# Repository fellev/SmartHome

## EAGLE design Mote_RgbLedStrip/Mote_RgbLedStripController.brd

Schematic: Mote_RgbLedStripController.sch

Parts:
ANALOGSIDE: M13; 1X13
DIGITALSIDE: M13; 1X13
J1: CON_TERMINAL_BLOCK_02-5MM; TERMINAL_BLOCK_2P_5

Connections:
A0: ANALOGSIDE.1
A1: ANALOGSIDE.2
A2: ANALOGSIDE.3
A3: ANALOGSIDE.4
A4_SDA: ANALOGSIDE.5
A5_SCL: ANALOGSIDE.6
A6: ANALOGSIDE.7
A7: ANALOGSIDE.8
D0_RX: ANALOGSIDE.9
D1_TX: ANALOGSIDE.10
D2: DIGITALSIDE.12
D3: DIGITALSIDE.11
D4: DIGITALSIDE.10
D5: DIGITALSIDE.9
D6: DIGITALSIDE.8
D7: DIGITALSIDE.7
D8: DIGITALSIDE.6
D9: DIGITALSIDE.5
D10_SS: DIGITALSIDE.4
D11_MOSI: DIGITALSIDE.3
D12_MISO: DIGITALSIDE.2
D13_SCK: DIGITALSIDE.1
GND: ANALOGSIDE.13, J1.1
PWR: ANALOGSIDE.12, J1.2
RST: DIGITALSIDE.13
VCC: ANALOGSIDE.11

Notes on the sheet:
12V

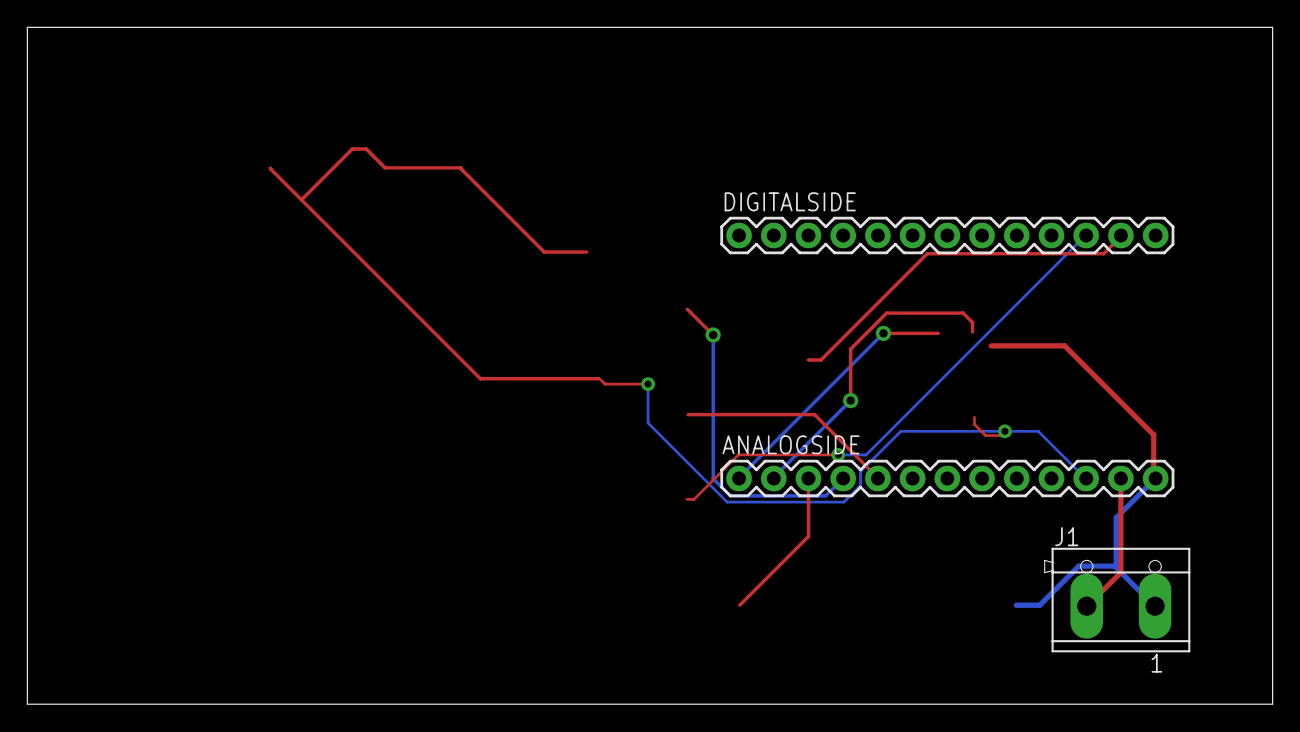
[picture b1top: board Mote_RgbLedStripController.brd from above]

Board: 2 copper layers, 91.1 x 49.5 mm, 3 parts (0 on the bottom side), 2 nets.

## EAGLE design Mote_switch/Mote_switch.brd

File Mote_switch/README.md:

Sync Mode
----------

Using SYNC mode (synchronize buttons on two SwitchMotes):

* Conect the sync wire to ground on switch you want to be controlled (the slave)
* Select the button mode (ON or OFF) by pressing the controlled button. Press the controlled button for 3 seonds. Now the switch in SYNC mode. Mode is ON when LED Duty Cycle is above 80% and OFF below 20%
* walk to the Mote_switch from which you want to control and ground the sync button and then press 3 seconds the button you want to be the controller (the master). At this point the master will broadcast a SYNC? token and the slave will respond with a SYNCx:y token where x=button placed in SYNC, y=mode of button placed in SYNC

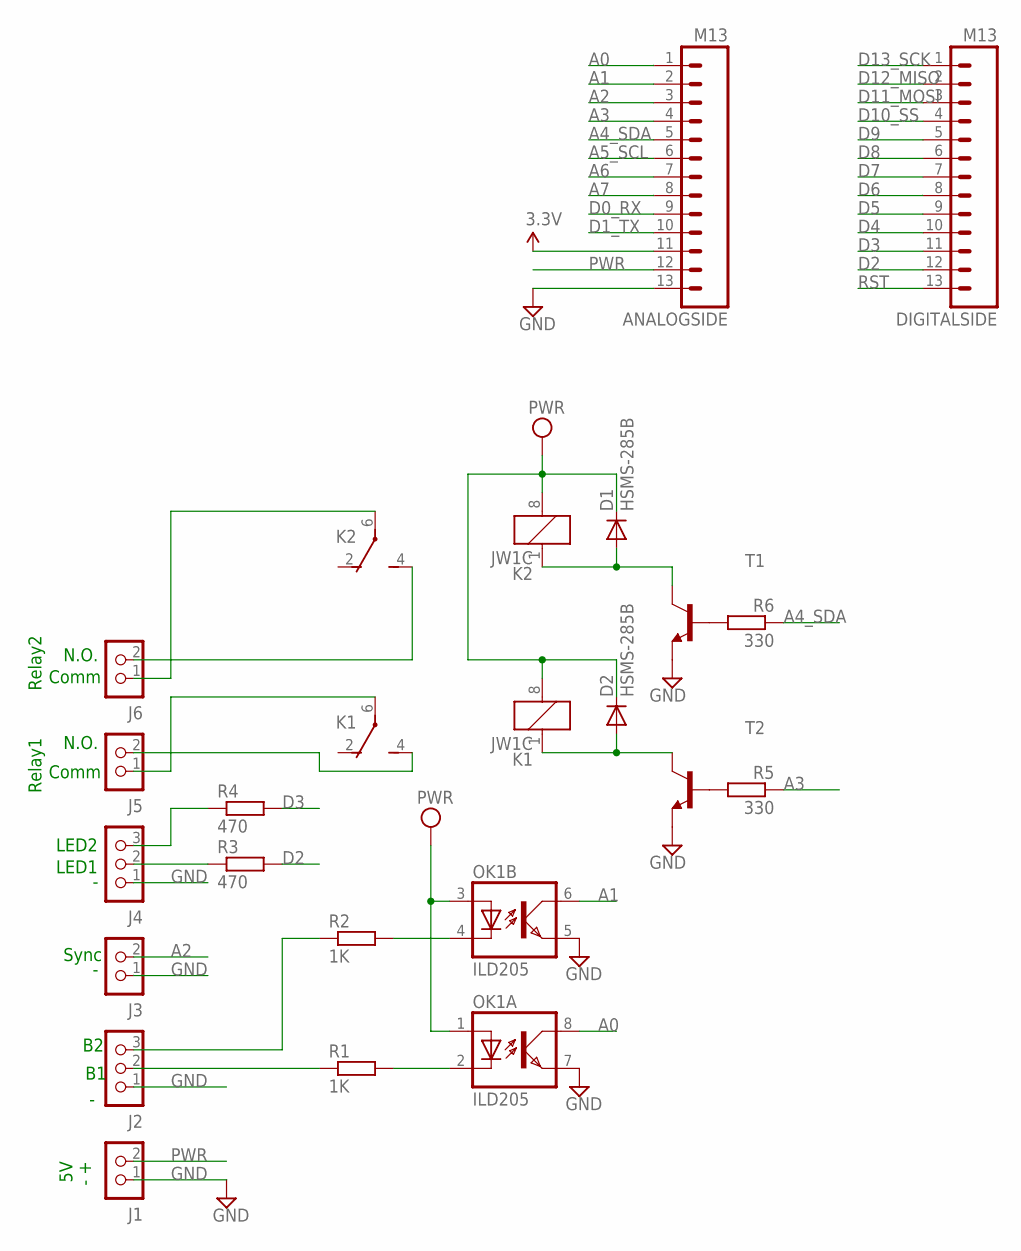
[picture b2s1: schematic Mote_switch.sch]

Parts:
ANALOGSIDE: M13; 1X13
D1, D2: HSMS-285B; SOT323
DIGITALSIDE: M13; 1X13
J1, J3, J5, J6: CON_TERMINAL_BLOCK_02-5MM; TERMINAL_BLOCK_2P_5
J2, J4: CON_TERMINAL_BLOCK_03-5MM; TERMINAL_BLOCK_3P_5
K1, K2: JW1C
OK1: ILD205; SOIC08
R1, R2: 1K; M2012
R3, R4: 470; M2012
R5, R6: 330; M2012
T1, T2: MMBT2222ALT1-NPN-SOT23-BEC; SOT23-BEC

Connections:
A0: ANALOGSIDE.1, OK1.8 (COL)
A1: ANALOGSIDE.2, OK1.6 (COL)
A2: ANALOGSIDE.3, J3.2
A3: ANALOGSIDE.4, R5.1
A4_SDA: ANALOGSIDE.5, R6.1
A5_SCL: ANALOGSIDE.6
A6: ANALOGSIDE.7
A7: ANALOGSIDE.8
D0_RX: ANALOGSIDE.9
D1_TX: ANALOGSIDE.10
D2: DIGITALSIDE.12, R3.2
D3: DIGITALSIDE.11, R4.2
D4: DIGITALSIDE.10
D5: DIGITALSIDE.9
D6: DIGITALSIDE.8
D7: DIGITALSIDE.7
D8: DIGITALSIDE.6
D9: DIGITALSIDE.5
D10_SS: DIGITALSIDE.4
D11_MOSI: DIGITALSIDE.3
D12_MISO: DIGITALSIDE.2
D13_SCK: DIGITALSIDE.1
GND: ANALOGSIDE.13, J1.1, J2.1, J3.1, J4.1, OK1.5 (EMIT), OK1.7 (EMIT), T1.E, T2.E
unnamed: J2.2, R1.1
unnamed: OK1.2 (C), R1.2
unnamed: J2.3, R2.1
unnamed: OK1.4 (C), R2.2
unnamed: R5.2, T2.B
unnamed: J4.3, R4.1
unnamed: R6.2, T1.B
unnamed: J6.2, K2.4 (S)
unnamed: J4.2, R3.1
unnamed: D2.1 (A), K1.1, T2.C
unnamed: D1.1 (A), K2.1, T1.C
unnamed: J6.1, K2.6
unnamed: J5.1, K1.6
unnamed: J5.2, K1.4 (S)
PWR: ANALOGSIDE.12, J1.2
RST: DIGITALSIDE.13
VCC: ANALOGSIDE.11, D1.3 (C), D2.3 (C), K1.8 (2), K2.8 (2), OK1.1 (A), OK1.3 (A)

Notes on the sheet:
Sync
LED1
LED2
Comm
N.O.
Relay1
Relay2

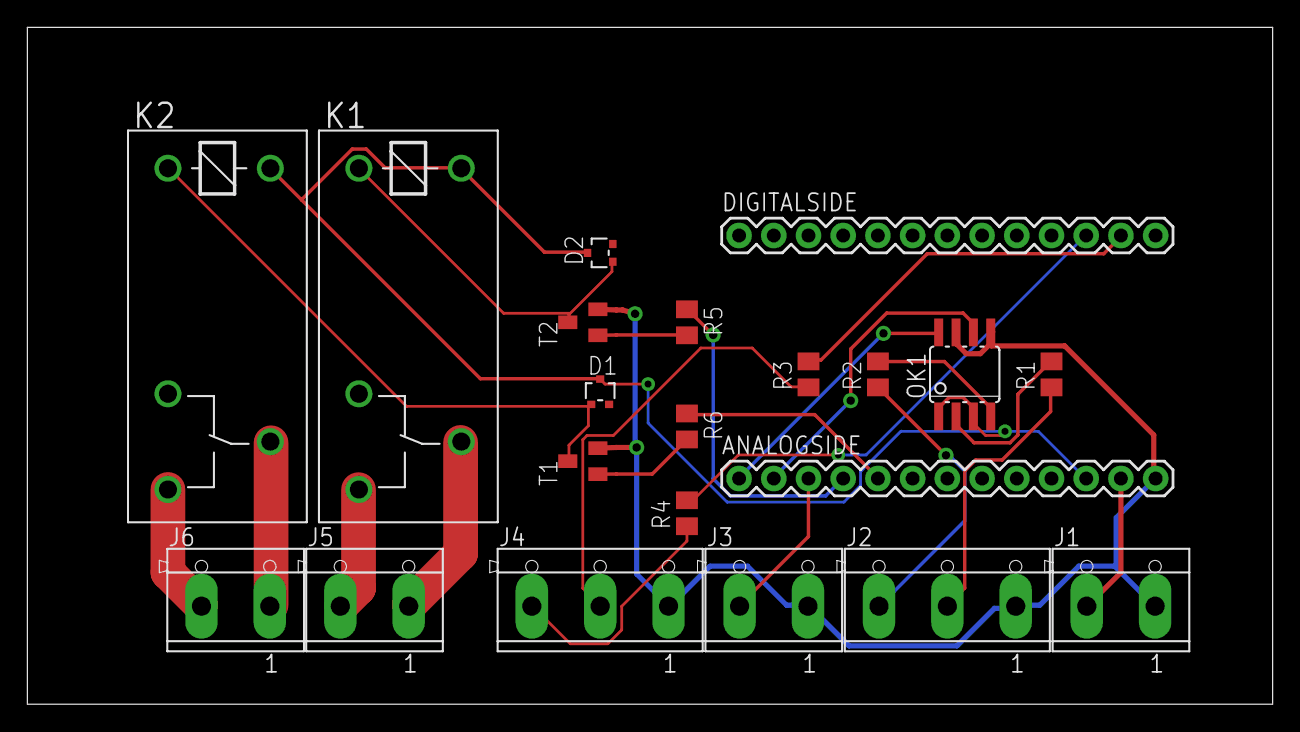
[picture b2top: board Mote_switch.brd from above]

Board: 2 copper layers, 91.1 x 49.5 mm, 21 parts (0 on the bottom side), 24 nets.

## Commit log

2014-12-10 Added 3 projects: Mote_gateway, Mote_shutter and piGateway
2014-12-10 Added SwitchMote project
2014-12-10 SwitchMote is removed
2014-12-10 Added new project: Mote_switch
2014-12-11 Minor update
2014-12-15 Added: Mote_switch schematics
2014-12-15 Mote_switch Sync process manual is updated
2014-12-16 Schematics updated
2014-12-22 Monor update
2015-01-07 Door movement timeout is increased
2015-02-10 Added STOP command to radio communication
2015-04-12 #!/bin/sh
    echo "starting pi gateway..."
    cd `dirname $0`
    ./piGatewayBase -v -s /dev/ttyUSB0 -t +
2015-09-10 Added support for rgb led strip in piGateway and Mote_gateway
2015-09-10 Added RGB led strip arduino sketch
2015-09-27 Added install rule to piGateway\nAdded script to start OpenHAB on boot
2016-01-04 + Added Schematics for RGB LED Controller + Added new project Mote_WirelessProgramming_gateway + Added new projetc Mote_setup + Added new project WirelessProgramming-master + SPI Flash library change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
2016-01-04 Added modified files
2016-01-09 * piGateway updated: Now it support multi LED RGB control
2016-01-28 * Mote_RgbLedStrip - Pin configuration has changed + Mote_irSender + IRrecord * GatewayBase - Added support for AC controller
2016-04-02 +Added: irSender project +Added mosquitto library for linux and arduino *Updated: OpenHAB configuration files
2016-04-02 *Updated: irSender *Updated: OpenHAB configuration files
2016-04-10 Added weather web app Air conditioner item values are backuped now
2016-05-30 added autorun install script for piGateway
2016-06-10 Improved RGB device handler Added but not finished switch device handler
2016-06-10 Removed invalid openhab start-on-boot configuration file
2016-06-10 Added new openhab start on boot configuration files
2016-07-08 Updated: openhab configurations
2016-10-11 Initial commit of SmartHomeWifi project
2016-10-12 Project wide update
2016-10-12 Added cleare eeprom command to mosquitto added hw config file
2016-10-15 Major update 1. Added input buttom for power on/off 2. Added pin to control power relay 3. Added led control when debug is disabled 4. Separted node id and in/out mqtt tipic
2016-10-16 +Added timers
2016-10-17 *Added control over external led - power indication
2016-10-22 Added mqtt port number to eeprom configuration Project wide major update
2016-10-28 1. Configuration server is active only if device is not connected to mqtt server. 2. Access to configuration web server is permitted only from soft AP 3. Web server handler implementation is changed 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
2016-11-12 +Added water heater *Openhab sitemap updated
2016-11-13 *Added manual power timer setting *Bug fix in timer post command
2016-11-13 +Added new eeprom erase profile
2016-11-14 Added rule that switch off water heater switch when off command recived from the device
2016-11-14 fixed mosquitto water heater power status path
2016-11-25 Added rule for water heater timer update during power ON
2017-07-28 Rollershutter is added to the kitchen
2018-02-17 Added Mote_irTranslator Updated Mote_irSender. Now device is responsive while sending ir codes
2018-02-17 NEC IR codes are enabled for IR translator
2018-12-08 Added openhab2 configuration
2018-12-22 Minor changes
2018-12-22 Added missing file
2019-09-07 Added debug mymosquitto address to openhab.cfg
2019-09-28 mqtt binding setting changed to legacy
2019-09-28 Living romm LED RGB setting is fixed. Added rule for Xiaomi Smart switch
2019-10-09 Added outside temperature Shelly's room renamed to Kids' room
2019-10-09 In sitemap ChildsRoom renamed to KidsRoom
2019-10-17 Fixed IR sender device type name Debug define is commented out
2019-10-17 Added rule for bedroom AC
2019-10-25 Feature: Added automatic AC power control
2019-10-25 Added Google calendar config file
2019-10-27 Feature: Added close all shutters and open all shutters items
2019-11-02 Feature: Added unified AC automatic power control function
2019-11-02 Feature: Water Heater project is migrated to new eclipse version eclipse-2019-06
2019-11-20 FEATURE: Added new Push buttoms for Living room and Bedroom
2019-11-21 FEATURE: Rules splitted to two files
2019-12-03 FEATURE: Added support for Samsung TV IR control
2019-12-03 FEATURE: Added support for TV IR control to MQTT Gateway
2019-12-07 FEATURE: piGateway is updated to work on banana pi platform
2019-12-07 FEATURE: In piGateway, TV message payload length is checked
2019-12-10 FEATURE: TV Remote support is added to Openhab
2020-01-11 Feature: Added stairs button
2020-03-07 Added Radiator to Kids Room
2020-04-10 Initial commit. LED PWM clock is 100 Hz using Timer1. LDR is connected to analog input
2020-04-10 added Arduino library movingAvg
2020-04-10 Added Mote_TvRemote directory
2020-04-10 spec.d is added to .gitignore
2020-04-10 .gitignore is updated
2020-04-10 file spec.d is deleted
2020-04-15 Added RPI4 Power Switch
2020-04-15 IR translator project ported to eclipse
2020-04-28 Added Bathroom heaters and some Sonoff devices ported to new MQTT bundle
2020-05-09 updated eclipse language.settings
2020-09-11 SmartHowWifi eclipse config files was updated
2020-09-19 Added new items rules rules
2020-09-20 Added light and AC switch to bedroom
2020-09-20 Added Openhab2 backup
2020-11-21 Feature: fading is now on all range
2020-12-26 Added Presense detection
2021-01-23 Added Radiator to 'turn off all AC' rule\n Added new backup
2021-07-17 Fixed water heater eclipe project
2021-08-15 Kitchen Roller Shutter replaced with Sonoff. + More chnages
2021-08-25 added Sonoff Kitchen shutter
2021-12-08 Sonoff 4ch livingroom & kitchen is updated
2021-12-11 4 ch sonoff configuration is updated
2023-03-03 Added tasmota configurations
2023-03-06 Somfy configuration update

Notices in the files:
parts and their libraries:
SparkFun-Connectors: Licensing: CC v3.0 Share-Alike You are welcome to use this library for commercial purposes.
